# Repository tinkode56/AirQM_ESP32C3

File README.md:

| Supported Targets | ESP32-C3 |
| ----------------- | -------- |

# AirQM_ESP32C3

Air quality monitor using ESP32-C3 and sensors to measure temperature, relative humidity, dust particles, CO2, VOC and NOx.

## Components used

|Item                       |Buy link                                                               |
|---------------------------|-----------------------------------------------------------------------|
| ESP32-C3 SuperMini        | [Aliexpress](https://www.aliexpress.com/item/1005006451672646.html)   |
| senseAir S8 004-0-0053    | [Aliexpress](https://www.aliexpress.com/item/1005005225848074.html)   |
| PMS5003                   | [Aliexpress](https://www.aliexpress.com/item/1005005967735332.html)   |
| SHT45                     | [Aliexpress](https://www.aliexpress.com/item/1005003742319869.html)   |
| SGP41                     | [Aliexpress](https://www.aliexpress.com/item/4000037083952.html)      |
| Oled Display              | [Aliexpress](https://www.aliexpress.com/item/32950307344.html)        |
| Magnets (5x3mm)           | [Aliexpress](https://www.aliexpress.com/item/1005001529831924.html)   |
| M2 set (M2A)              | [Aliexpress](https://www.aliexpress.com/item/1005005467831636.html)   |

## Hardware
```
Neodim magnet: 5mm diameter, 3mm height
Heat insert: M2 x 3 x 3.2 for main board
Screws: M2 for PMS5003
```

## Pin connection matrix

```
| ESP32-C3 |  OLED   |  SGP41  |  SHT45  | Senseair S8 | PMS5003  | WS2812 |
|----------|---------|---------|---------|-------------|----------|--------|
| GND      | Pin GND | Pin GND | Pin GND | G0          | PIN2 GND |        |
| 3V3      | Pin 3V3 | Pin 3V3 | Pin 3V3 |             |          |        |
| 5V       |         |         |         | G+          | PIN1 VCC |        |
| GPIO_0   |         |         |         |             | PIN4 TX  |        |
| GPIO_1   |         |         |         |             | PIN5 RX  |        |
| GPIO_2   |         |         |         |             |          |        |
| GPIO_3   |         |         |         |             |          |  DATA  |
| GPIO_4   | Pin SCK |         |         |             |          |        |
| GPIO_5   | Pin DC  |         |         |             |          |        |
| GPIO_6   | Pin SDA |         |         |             |          |        |
| GPIO_7   | Pin CS  |         |         |             |          |        |
| GPIO_8   |         | Pin SDA | Pin SDA |             |          |        |
| GPIO_9   |         | Pin SCL | Pin SCL |             |          |        |
| GPIO_10  | Pin RES |         |         |             |          |        |
| GPIO_20  |         |         |         | UART_TxD    |          |        |
| GPIO_21  |         |         |         | UART_RxD    |          |        |
```

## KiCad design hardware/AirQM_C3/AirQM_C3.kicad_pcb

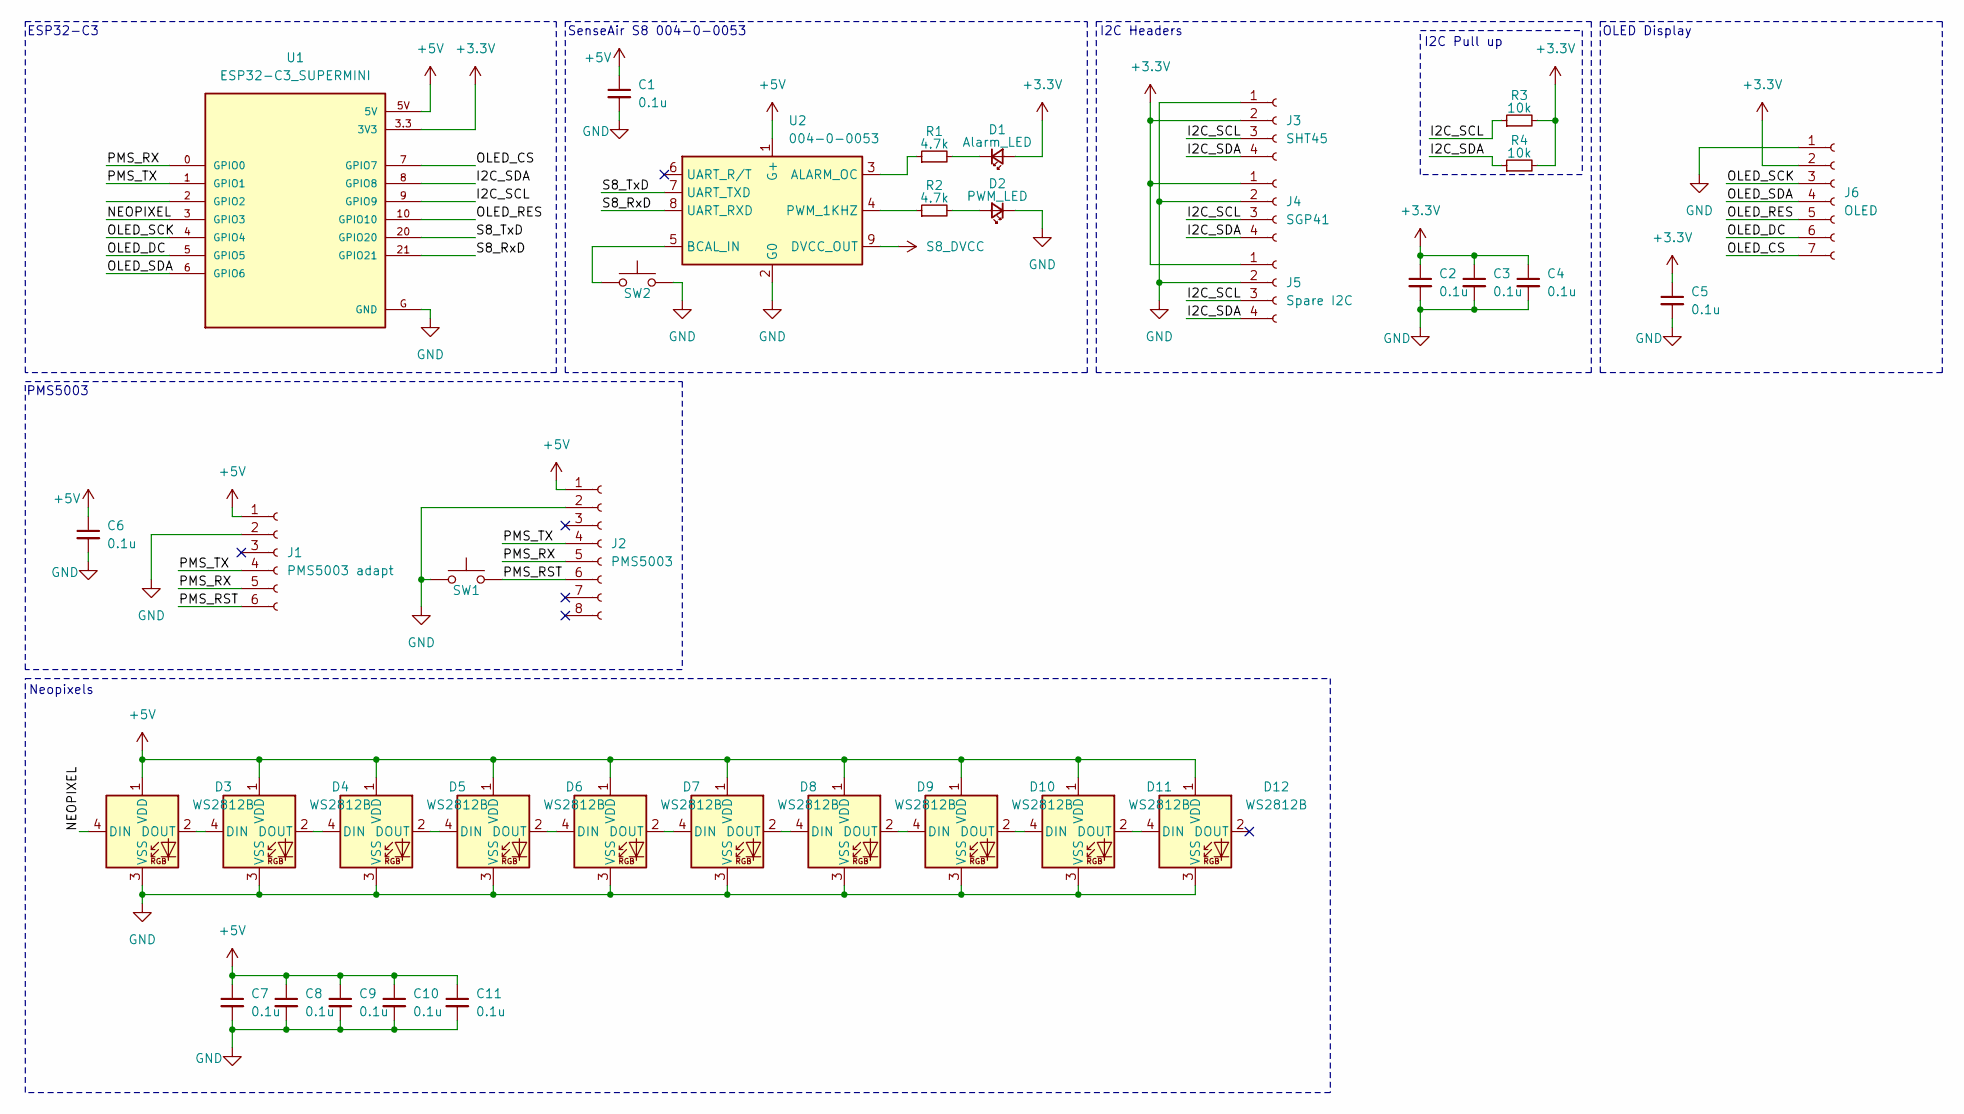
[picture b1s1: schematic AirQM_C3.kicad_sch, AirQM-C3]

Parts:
C1, C2, C3, C4, C5, C6, C7, C8, C9, C10, C11: 0.1u; C_0603_1608Metric
D1: Alarm_LED; LED_0805_2012Metric
D2: PWM_LED; LED_0805_2012Metric
D3, D4, D5, D6, D7, D8, D9, D10, D11, D12: WS2812B; ws2812_airqm
J1: PMS5003 adapt; PinSocket_1x06_P2.54mm_Vertical
J2: PMS5003; Molex_PicoBlade_53261-0871_1x08-1MP_P1.25mm_Horizontal
J3: SHT45; PinSocket_1x04_P2.54mm_Vertical
J4: SGP41; PinSocket_1x04_P2.54mm_Vertical
J5: Spare I2C; PinSocket_1x04_P2.54mm_Vertical
J6: OLED; PinSocket_1x07_P2.54mm_Vertical
R1, R2: 4.7k; R_0805_2012Metric
R3, R4: 10k; R_0805_2012Metric
SW1, SW2: SW_Push; tactile_switch_airqm
U1: ESP32-C3_SUPERMINI; MODULE_ESP32-C3_SUPERMINI
U2: 004-0-0053; Senseair_S8_Up

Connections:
+3.3V: C2.1, C3.1, C4.1, C5.1, D1.2 (A), J3.2, J4.1, J5.1, J6.2, R3.2, R4.2, U1.3.3 (3V3)
+5V: C1.1, C6.1, C7.1, C8.1, C9.1, C10.1, C11.1, D3.1 (VDD), D4.1 (VDD), D5.1 (VDD), D6.1 (VDD), D7.1 (VDD), D8.1 (VDD), D9.1 (VDD), D10.1 (VDD), D11.1 (VDD), D12.1 (VDD), J1.1, J2.1, U1.5V, U2.1 (G+)
/I2C_SCL: J3.3, J4.3, J5.3, R3.1, U1.9 (GPIO9)
/I2C_SDA: J3.4, J4.4, J5.4, R4.1, U1.8 (GPIO8)
/NEOPIXEL: D3.4 (DIN), U1.3 (GPIO3)
/OLED_CS: J6.7, U1.7 (GPIO7)
/OLED_DC: J6.6, U1.5 (GPIO5)
/OLED_RES: J6.5, U1.10 (GPIO10)
/OLED_SCK: J6.3, U1.4 (GPIO4)
/OLED_SDA: J6.4, U1.6 (GPIO6)
/PMS_RST: J1.6, J2.6, SW1.2
/PMS_RX: J1.5, J2.5, U1.0 (GPIO0)
/PMS_TX: J1.4, J2.4, U1.1 (GPIO1)
/S8_RxD: U1.21 (GPIO21), U2.8 (UART_RXD)
/S8_TxD: U1.20 (GPIO20), U2.7 (UART_TXD)
GND: C1.2, C2.2, C3.2, C4.2, C5.2, C6.2, C7.2, C8.2, C9.2, C10.2, C11.2, D2.1 (K), D3.3 (VSS), D4.3 (VSS), D5.3 (VSS), D6.3 (VSS), D7.3 (VSS), D8.3 (VSS), D9.3 (VSS), D10.3 (VSS), D11.3 (VSS), D12.3 (VSS), J1.2, J2.2, J2.MP, J3.1, J4.2, J5.2, J6.1, SW1.1, SW2.2, U1.G (GND), U2.2 (G0)
unnamed: D1.1 (K), R1.2
unnamed: D2.2 (A), R2.2
unnamed: D3.2 (DOUT), D4.4 (DIN)
unnamed: D4.2 (DOUT), D5.4 (DIN)
unnamed: D5.2 (DOUT), D6.4 (DIN)
unnamed: D6.2 (DOUT), D7.4 (DIN)
unnamed: D7.2 (DOUT), D8.4 (DIN)
unnamed: D8.2 (DOUT), D9.4 (DIN)
unnamed: D9.2 (DOUT), D10.4 (DIN)
unnamed: D10.2 (DOUT), D11.4 (DIN)
unnamed: D11.2 (DOUT), D12.4 (DIN)
unnamed: R1.1, U2.3 (ALARM_OC)
unnamed: SW2.1, U2.5 (BCAL_IN)
unnamed: R2.1, U2.4 (PWM_1KHZ)
S8_DVCC: U2.9 (DVCC_OUT)

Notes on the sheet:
I2C Pull up
I2C Headers
PMS5003
SenseAir S8 004-0-0053
Neopixels
OLED Display
ESP32-C3

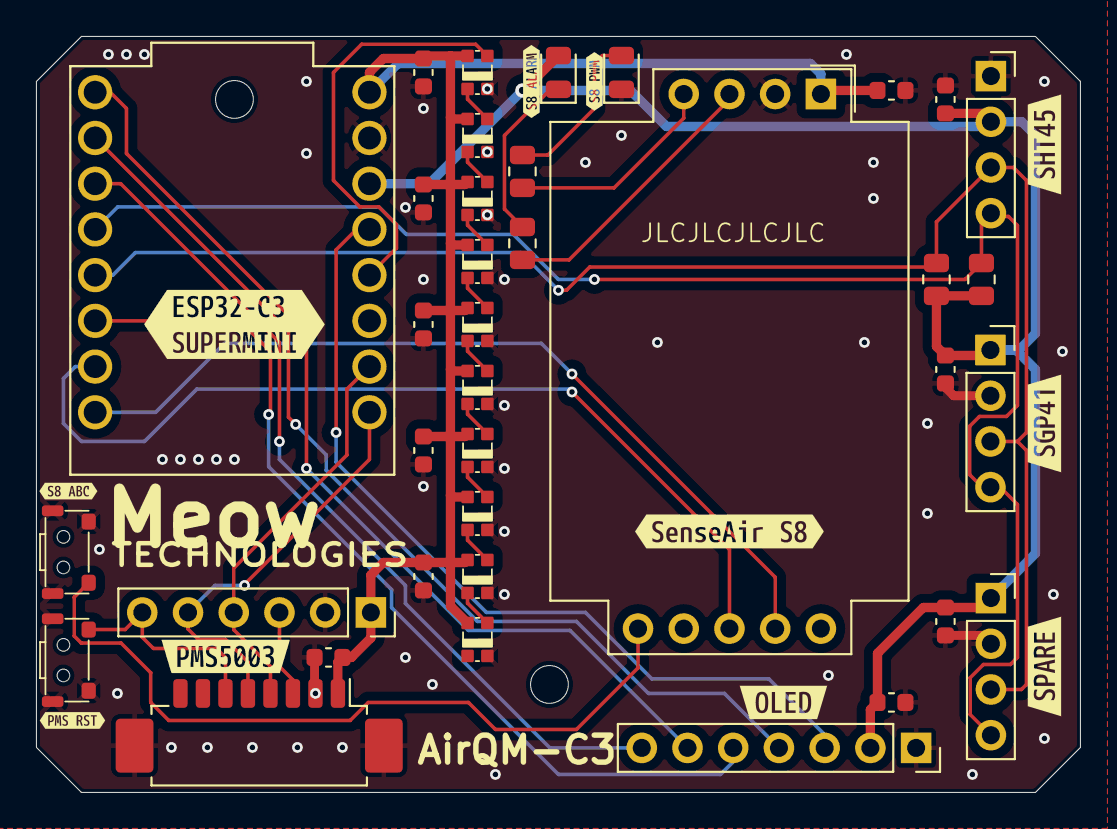
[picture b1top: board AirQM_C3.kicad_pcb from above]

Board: 2 copper layers, 58.0 x 42.0 mm, 48 parts (0 on the bottom side), 30 nets.

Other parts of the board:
kibuzzard-660842A3: G***; kibuzzard-660842A3
kibuzzard-660842BE: G***; kibuzzard-660842BE
kibuzzard-660842DD: G***; kibuzzard-660842DD
kibuzzard-660842F1: G***; kibuzzard-660842F1
kibuzzard-6608425C: G***; kibuzzard-6608425C
kibuzzard-6608431D: G***; kibuzzard-6608431D
kibuzzard-66084205: G***; kibuzzard-66084205
kibuzzard-66084210: G***; kibuzzard-66084210
kibuzzard-66084234: G***; kibuzzard-66084234
kibuzzard-66084249: G***; kibuzzard-66084249
kibuzzard-66084324: G***; kibuzzard-66084324

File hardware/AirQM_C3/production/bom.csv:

Designator,Footprint,Quantity,Value,LCSC Part #
"C1, C10, C11, C2, C3, C4, C5, C6, C7, C8, C9",0603,11,0.1u,
D1,0805,1,Alarm_LED,
"D10, D11, D12, D3, D4, D5, D6, D7, D8, D9",ws2812_airqm,10,WS2812B,
D2,0805,1,PWM_LED,
J1,PinSocket_1x06_P2.54mm_Vertical,1,PMS5003 adapt,
J2,Molex_PicoBlade_53261-0871_1x08-1MP_P1.25mm_Horizontal,1,PMS5003,
J3,PinSocket_1x04_P2.54mm_Vertical,1,SHT45,
J4,PinSocket_1x04_P2.54mm_Vertical,1,SGP41,
J5,PinSocket_1x04_P2.54mm_Vertical,1,Spare I2C,
J6,PinSocket_1x07_P2.54mm_Vertical,1,OLED,
"R1, R2",0805,2,4.7k,
"R3, R4",0805,2,10k,
"SW1, SW2",tactile_switch_airqm,2,SW_Push,
U1,MODULE_ESP32-C3_SUPERMINI,1,ESP32-C3_SUPERMINI,
U2,Senseair_S8_Up,1,004-0-0053,

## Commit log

2024-03-18 Enable configuration for builtin JTAG debug + svd file
2024-03-18 Small readme update
2024-03-19 MODBUS implementation beginning
2024-03-19 Drop MODBUS library usage, will implement dedicated solution specific to sensor
2024-03-20 Migrate project to latest ESP-IDF version (master) to fix issue with bootloader using JTAG/USB for logging messages
2024-03-21 Complete driver for SenseairS8 CO2 sensor Reintroduced freemodbus component
2024-03-23 Integrate driver for PMS5003 Add documentation for each device used Test code for sending periodic messages to a future WiFi task Code cleanup Updates to README
2024-03-25 Added WiFi connectivity, NTP time sync, write data to InfluxDB
2024-03-27 Create dedicated tasks for handling sensor data One task responsible for receiving all sensor data and sending to OLED task in order to update the screen One task responsible for handling time synchr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
2024-03-28 Small FreeRTOS stack overflow change + Kconfig typo fix
2024-04-01 Task stack resize, update readme KiCad project added with schematic and PCB
2024-04-04 Hardware update
2024-04-04 SDK config updates
2024-05-19 Add neopixel support
2024-07-12 Board configuration file created
2024-07-13 IDF version update, add neopixel working code
2024-07-18 Multiple changes to architecture Add correct task priorities Sync NTP at boot only instead of every minute, let lwIP sync automatically each hour
2024-09-09 Splash screen implementation Now until the connection to WiFi is done and the first set of data is acquired from sensors, the display shows a custom logo
